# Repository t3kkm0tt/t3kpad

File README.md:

# t3kpad
by t3kkm0tt
I was doing this for hackpad.hackclub.com and here is my submission!

Here an image of the fully assembled pcb... not very detailed.

The schematic:

The PCB:

And an image of the case and how it fits together...lol

BOM:
	
 	12 SK6812mini leds
 	(1 soldering iron)
	6 mx 1.00u switches (solderable)
 	1 XIAO-RP-2040-DIP

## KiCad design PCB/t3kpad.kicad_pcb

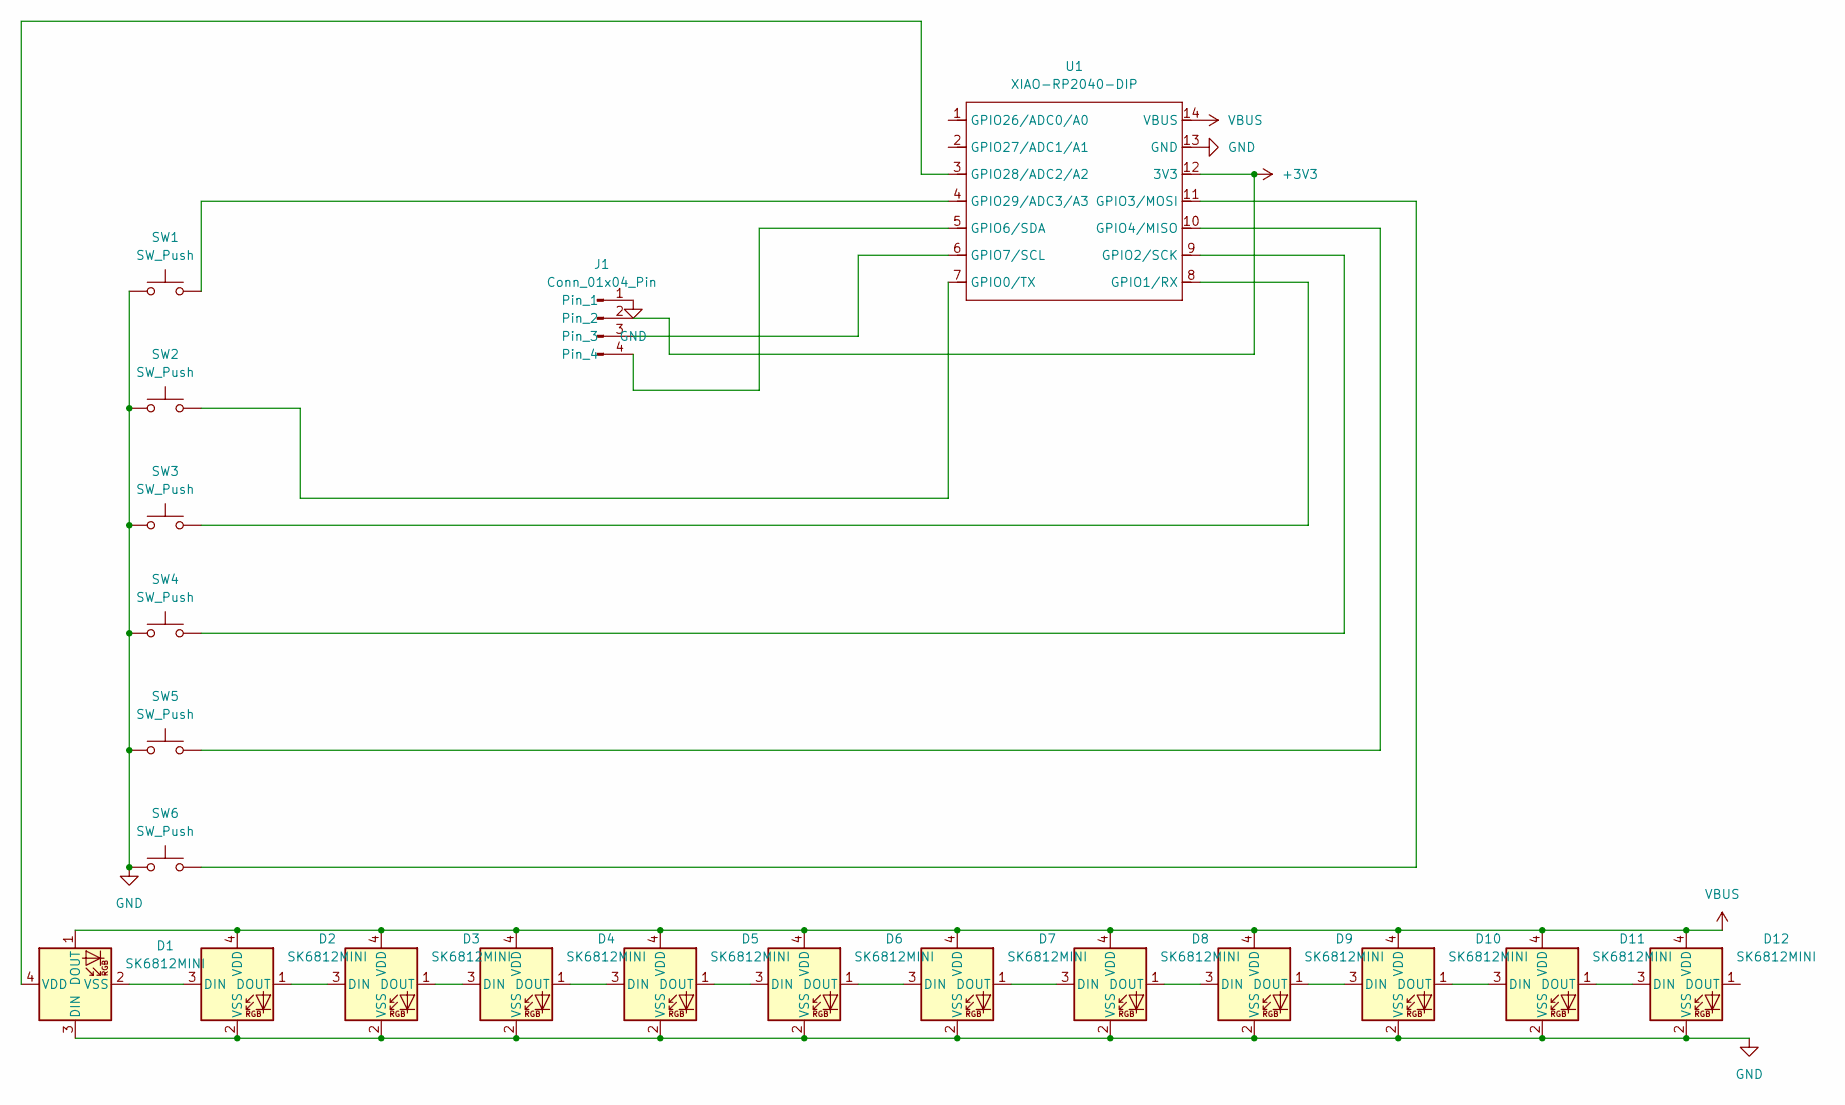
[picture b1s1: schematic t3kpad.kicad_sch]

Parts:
D1, D2, D3, D4, D5, D6, D7, D8, D9, D10, D11, D12: SK6812MINI
J1: Conn_01x04_Pin; SSD1306-0.91-OLED-4pin-128x32
SW1, SW2, SW3, SW4, SW5, SW6: SW_Push; MX_PCB_1.00u
U1: XIAO-RP2040-DIP

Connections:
+3V3: J1.2, U1.12 (3V3)
GND: D1.3 (DIN), D2.2 (VSS), D3.2 (VSS), D4.2 (VSS), D5.2 (VSS), D6.2 (VSS), D7.2 (VSS), D8.2 (VSS), D9.2 (VSS), D10.2 (VSS), D11.2 (VSS), D12.2 (VSS), J1.1, SW1.1, SW2.1, SW3.1, SW4.1, SW5.1, SW6.1, U1.13 (GND)
unnamed: D1.4 (VDD), U1.3 (GPIO28/ADC2/A2)
unnamed: D1.2 (VSS), D2.3 (DIN)
unnamed: D2.1 (DOUT), D3.3 (DIN)
unnamed: D3.1 (DOUT), D4.3 (DIN)
unnamed: D4.1 (DOUT), D5.3 (DIN)
unnamed: D5.1 (DOUT), D6.3 (DIN)
unnamed: D6.1 (DOUT), D7.3 (DIN)
unnamed: D7.1 (DOUT), D8.3 (DIN)
unnamed: D8.1 (DOUT), D9.3 (DIN)
unnamed: D9.1 (DOUT), D10.3 (DIN)
unnamed: D10.1 (DOUT), D11.3 (DIN)
unnamed: D11.1 (DOUT), D12.3 (DIN)
unnamed: J1.3, U1.6 (GPIO7/SCL)
unnamed: J1.4, U1.5 (GPIO6/SDA)
unnamed: SW2.2, U1.7 (GPIO0/TX)
unnamed: SW3.2, U1.8 (GPIO1/RX)
unnamed: SW4.2, U1.9 (GPIO2/SCK)
unnamed: SW6.2, U1.11 (GPIO3/MOSI)
unnamed: SW5.2, U1.10 (GPIO4/MISO)
unnamed: SW1.2, U1.4 (GPIO29/ADC3/A3)
VBUS: D1.1 (DOUT), D2.4 (VDD), D3.4 (VDD), D4.4 (VDD), D5.4 (VDD), D6.4 (VDD), D7.4 (VDD), D8.4 (VDD), D9.4 (VDD), D10.4 (VDD), D11.4 (VDD), D12.4 (VDD), U1.14 (VBUS)

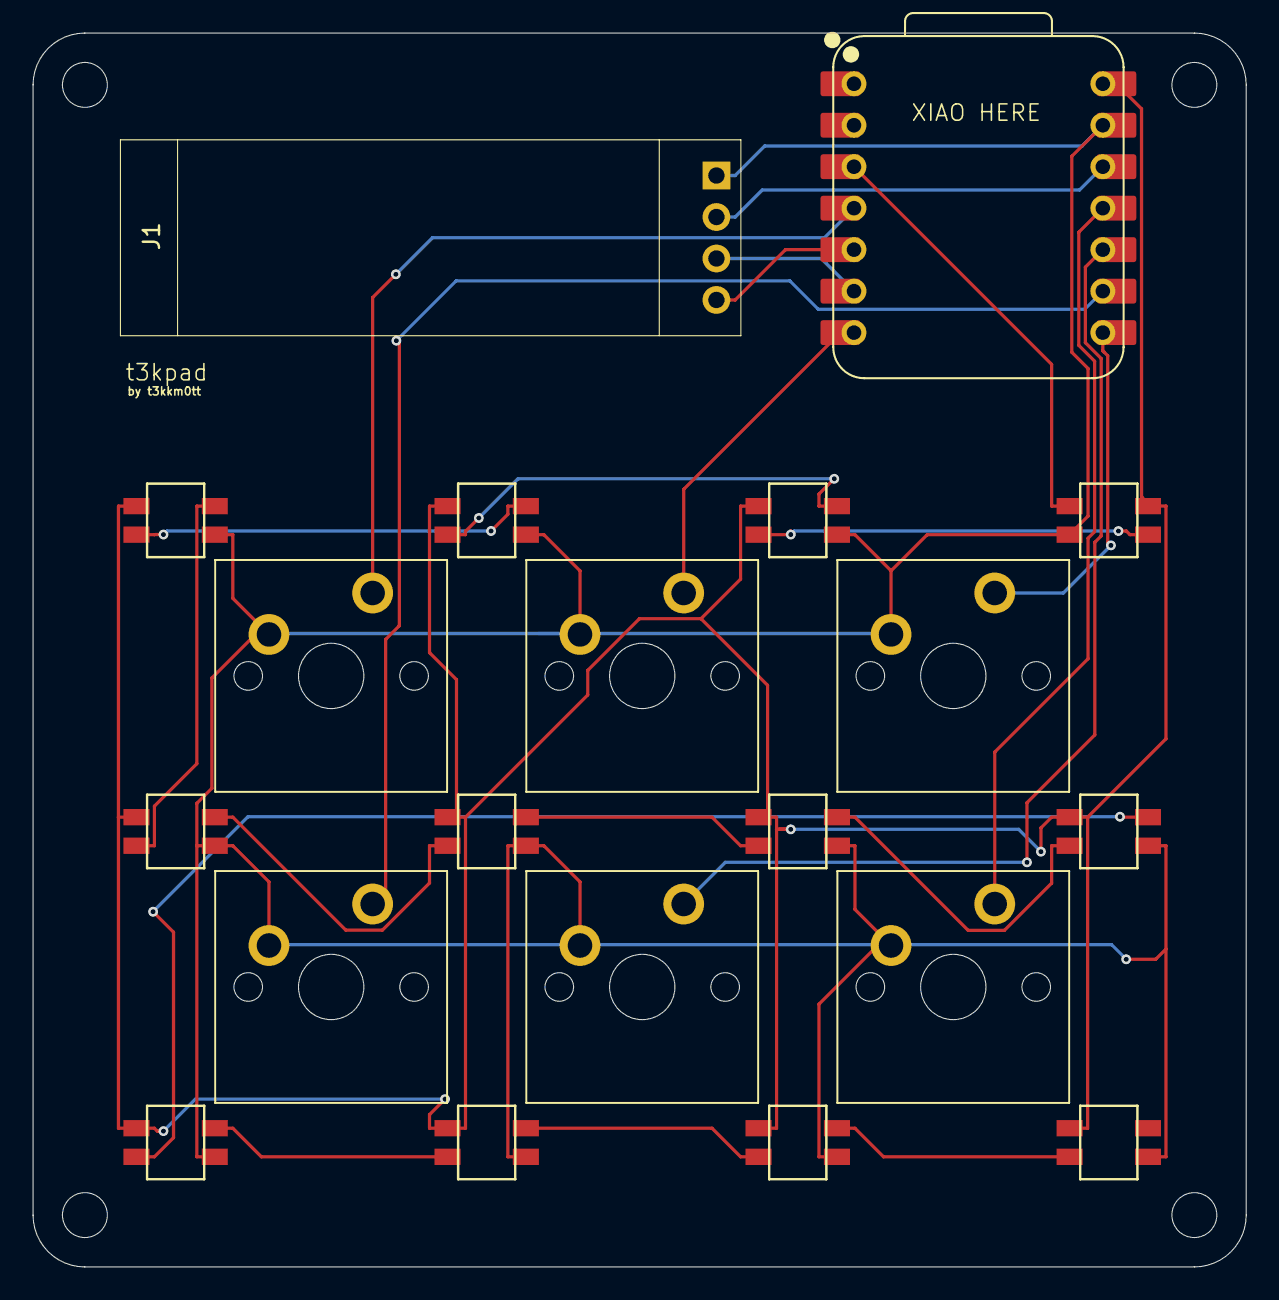
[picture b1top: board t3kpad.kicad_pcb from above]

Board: 2 copper layers, 74.3 x 75.6 mm, 20 parts (0 on the bottom side), 23 nets.

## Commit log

2025-06-21 i love cats meow
2025-07-02 meow
